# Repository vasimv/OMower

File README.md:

OMower project is open-source open-hardware wheeled robots platform with 32-bit ARM ATSAM3X8E
microcontroller, same as in Arduino Due. The project compiles under Arduino IDE (requires patching standard
ATSAM platform library files to support all GPIO lines of the MCU).

The project was inspired by ardumower project (https://github.com/Ardumower/ardumower) and uses few bits
of its code.

FEATURES

Control, measurements and navigation routines for wheeled robots (primarily lawn mowers but not limited to)
with wire perimeters, sonars and other sensors, GPS or RTK GPS (centimeters-level precision).

Support for 2 (with third support wheel) or 4 motors platforms. Brushed motors supported with Polulu Dual
MC33926 (onboard) or IHM12A1 controllers (external), brushless motors will require external ESCs (controlled
by PPM/servo output).

Includes PPM/servo output for the brushless mowing motor (or you may use onboard for brushed mowing motor)
and step-motor drivers for cutter's height adjusting.  

Supports many communication ports of ATSAM3X8E with onboard connectors to connect almost everything. 

It may operate with pure pfodApp (or Modbus) user interface but has limited support for Robot OS (ROS).

HARDWARE

The board is based on ATSAM3X8E-AU MCU in 144-pins LQFP case (for arduino IDE it looks like Arduino Due
without "programming" port).

Power subsystem includes step-down charging regulator (up to 4A charging current) and step-up for solar
battery, bi-stable relay for emergency shutdown. Has 3 switching regulators to provide 3.3V and 5V to
multiple internal and external devices, precise linear regulator for analog parts.

Supports battery voltages up to 28 volts, has onboard switching regulators for external charger and solar
panel.

Three ACS725-30 current hall sensors to measure consumption and charging currents up to 30A real-time.

Multiple connectors for everything mower or any other robot needed with 5V->3.3V logic conversion (6x HC-SR04
sonars, 5 odometers, 3 serial ports, 4 wire perimeter sensors, two bumper sensors, lawns and drops sensors,
two temperature NTC termistors connectors, two SPI ports, LEDs, button and more).

Has I2C buffers (both 3.3V and 5V versions) to connect multiple I2C devices, USB port (firmware upload),
external 12-channel ADC MAX11617 (connected to I2C).

Has port for Orange PI Zero (for RTK GPS and Wifi connectivity, firmware upload), can be replaced by any
Wifi/Bluetooth adapter connected to serial port of MCU.

Multiple PPM/servo outputs for external stuff with standard 3-pins connectors.

Note, board requires external components: external IMU GY-80 board or MPU-9250 board, external motors
controllers and steppig motor driver boards. External charger voltage must be 6 volts higher than
maximum battery voltage (i.e. for 14.6V LiFePo-battery it must provide 20..34V).

Latest version is 3, in v4 version the board will include FRAM chip to store settings/waypoints/etc (as
ATSAM3X8E's flash is getting erased when uploading new firmware) and onboard IMU MPU9250.

Schematics and KiCad development files for the 4-layers board is in hardware folder. Version 3 board
variant can be ordered from oshpark: https://oshpark.com/shared_projects/ILEdXK2T

SOFTWARE

The SDK's main goal is isolate hardware stuff from higher level software and easy development of wheeled
robot platforms. It configures timers, interrupts, ADCs and other stuff to provide API to develop software
without underlying hardware knowledge. It provides basic control and navigation stuff (like moving between
points with RTK GPS), external ports (like sonars or PPM/servo stuff), measurements for ADCs (internal and
onboard MAX11617), etc.

Look omower-*.h header files for API classes, check OMower_Simple firmware to see how to use them.

OMower SDK includes patches (see *.patch files) for standard ATSAM* libraries to support all GPIO's of
ATSAM3X8E (compatible GPIO mapping with Taijuino Due Pro). Without them you won't able to use all ports of
the OMower board!

Some of OMower stuff is not compatible with other arduino libraries, check restrictions.txt file.

Decawave DWM1000 radiotags navigation support is not tested yet, requires DWM1000 tags connected to MCU with
MyRangeTag software, see https://github.com/vasimv/MyRangeTag

USAGE

Place OMower folder into ~/Arduino/libraries, choose your board in omower-defs.h (currently supported boards
are OMower v3 and Arduino Due + IHM12A1 motor controller. Remember to patch ATSAM hardware library files to
use all GPIOs of ATSAM3X8E MCU.

Clone https://github.com/vasimv/OMower_Simple and  put its folder into ~/Arduino, compile and upload. Use
pfodApp to control the robot.

ROS support

At this moment, ROS support is limited and includes sending some of sensors data to ROS (with *MultiArray
messages but i planning to convert them to standartized message types), /cmd_vel support and routing debug and user
interface to ROS topics. See OMower_Simple firmware example on how to enable ROS in your firmware.

HOW IT WORKS

OMower software must define all needed objects, set pointers to other objects where it needed (like
gps object needs to set pointer to imu object), call all begin() functions of objects (hardware init, called
just once), then sets values for objects parameters and call init() functions (software init, can be
called many times to reset the object's hardware), define poll10/20/50 hooks functions to call objects
poll*() functions from there (see OMower_Simple.ino for example).

One of most important classes is motors object (see omower-motors.h), it controls motor drivers from its
poll10() function. User just calls functions roll/move (to simple turning or driving in a specific
direction) or rollCourse/MoveCourse to drive with navigation by something (compass, gps, etc). 

IMU stuff (compass, gyro, accelerometer) are read in imu object (omower-imu.h) by its poll50() function.
It does filtering/calculation and provide angle values for compass and pitch/yaw/roll in degrees
(see omower-imu.h). The imu object is daughter class of navThing class (see omower-root.h) that means
it has readCourseError() function, so it can be used for navigation by motors object. Currently it supports
navigation by compass angle.

GPS object is daughter class of navThing too, so it supports navigation. All coordinates are stored in
int32_t values (so, 18.3495,-68.5960 will be 183495000,-685960000 actually) to improve precision (otherwise
it would need large float class which does not exists in arduino framework). The user software must
interface with a GPS receiver and feed NMEA lines from it to gps::parseString() function or raw
coordinates to gps::settCoords() (see omower-gps.h). In precision mode (when centimeters-precise
coordinates are used) - the gps object calculates robot's true coordinates using offset of GPS's antenna
(distance from robot's center and angle).

Power object (omower-power.h) handles power stuff (battery, solar panel and charger regulators) and
provides human-readable values of voltages and currents.

Mow object (omower-mow.h) manages the mowing motor(s) and its actuator (if have) to adjust cutting height.
Note, currently it supports only PPM regulation on PWM-E output (brushless motors ESC connected to it), but
will support brushed motors too (in 2 wheel motors + mow motor configuration).

Perimeter object (omower-perimeter.h) supports up to 4 wire perimeter sensors (same as for ardumower, just
inductor+analog amplifier).

Serial object (omower-serial.h) handles communication with serial ports (as you can't use arduino's
objects for that because possible interrupts conflicts). It has also better printf() functions which
supports %f/%g for floats. UART (Serial.*) interface works with DMA (through built-in PDC) with huge
output buffer (2048 bytes, can be changed in omower-debug.h), so debug output function won't cause
slow-downs.

Sonars object (omower-sonars.h) handles HC-SR04 sonars (up to 6). It returns sonar's reported distance
(in centimeters) through its readSonar() function. Since motors routines do not check for any obstacles
during movement (except overcurrent on motors drivers), the user software must check sonars and bumpers
to avoid obstacles and move around them.

At start of initialization chassis object (omower-chassis.h) initializes interrupts. This is most important
task as almost all of OMower's stuff is done through interrupts hooks. It configures TIM7 to generate
interrupts 100 times per second.

At every TIM7 interrupt, it reads 12 channels of MAX11617 ADC to "uint16_t adc11617Arr[]"
(defined in max11617-adc-scan.h), this array is accessed from other OMower's objects (like power object, but
of course you can read its values directly).

Every second cycle of TIM7 interrupt it calls user's poll50() hook, at every fifth - poll20() hook, at
every tenth - poll10(). User's software must define these functions, set it through
chassis::setHooksPoll() function and call all other objects poll10/20/50 functions from there. By default,
to call hook functions it creates software interrupts for each kind of them (defined symbol
USE_SOFTWARE_INTERRUPTS in omower-defs-omowerv3.h), so they are running asynchronous. Without
USE_SOFTWARE_INTERRUPTS - poll50/20/10 hooks called after each other and you are limited to 20ms total time
for all of them (OMower SDK functions were optimized to comply with that time and software interrupts
can be turned off but if you place some other CPU hungry stuff in it - you will need software interrupts).

It was possible to create automatic binding for poll functions (so user wouldn't need to call all
objects poll*() functions from firmware code), but it was decided not to do so to simplify the SDK
internals.

All internal ADC channels of ATSAM3X8E are read by separate TIM5 interrupts 38461 times per second to the
"adcArr[]" array (see due-adc-scan.h for its structure). This array is accessed by other omower objects
from their poll10/20/50 functions, so no need to read it directly (but you still can do). Note, it is
possible to add circle buffer to every channel read, so you won't miss any of value (this method is used
in wire perimeter class for FFT filtering of the perimeter signal) through adcAddChannel()
function (due-adc-scan.h).

PWM and TCC (in PWM mode) outputs are configured through pwmServo object (omower-pwmservo.h), don't use
other methods to modify their output as it may conflict with OMower code. Since the code uses some
MCU's timers, you won't able to use these for other things (Timer0, Timer6, Timer8 in pwmServo, Timer5 in
due-adc-scan.cpp, Timer7 in chassis). Usually, nothing uses them but some of arduino libraries do (like
Servo library, which you wouldn't need as there is pwmServo object).

Debug function debug() is defined in omower-debug.h. By default, it sends its output to Serial device, has
ability to set priority for debug messages (so low-priority stuff won't be send at all).

There are some other objects which are easy to understand (omower-rtc.h for RTC clock, omower-current*.h for
current sensors, omower-odometry.h for odometry sensors), please, look their header files and OMower_Simple
firmware code if you want to know how they are used.

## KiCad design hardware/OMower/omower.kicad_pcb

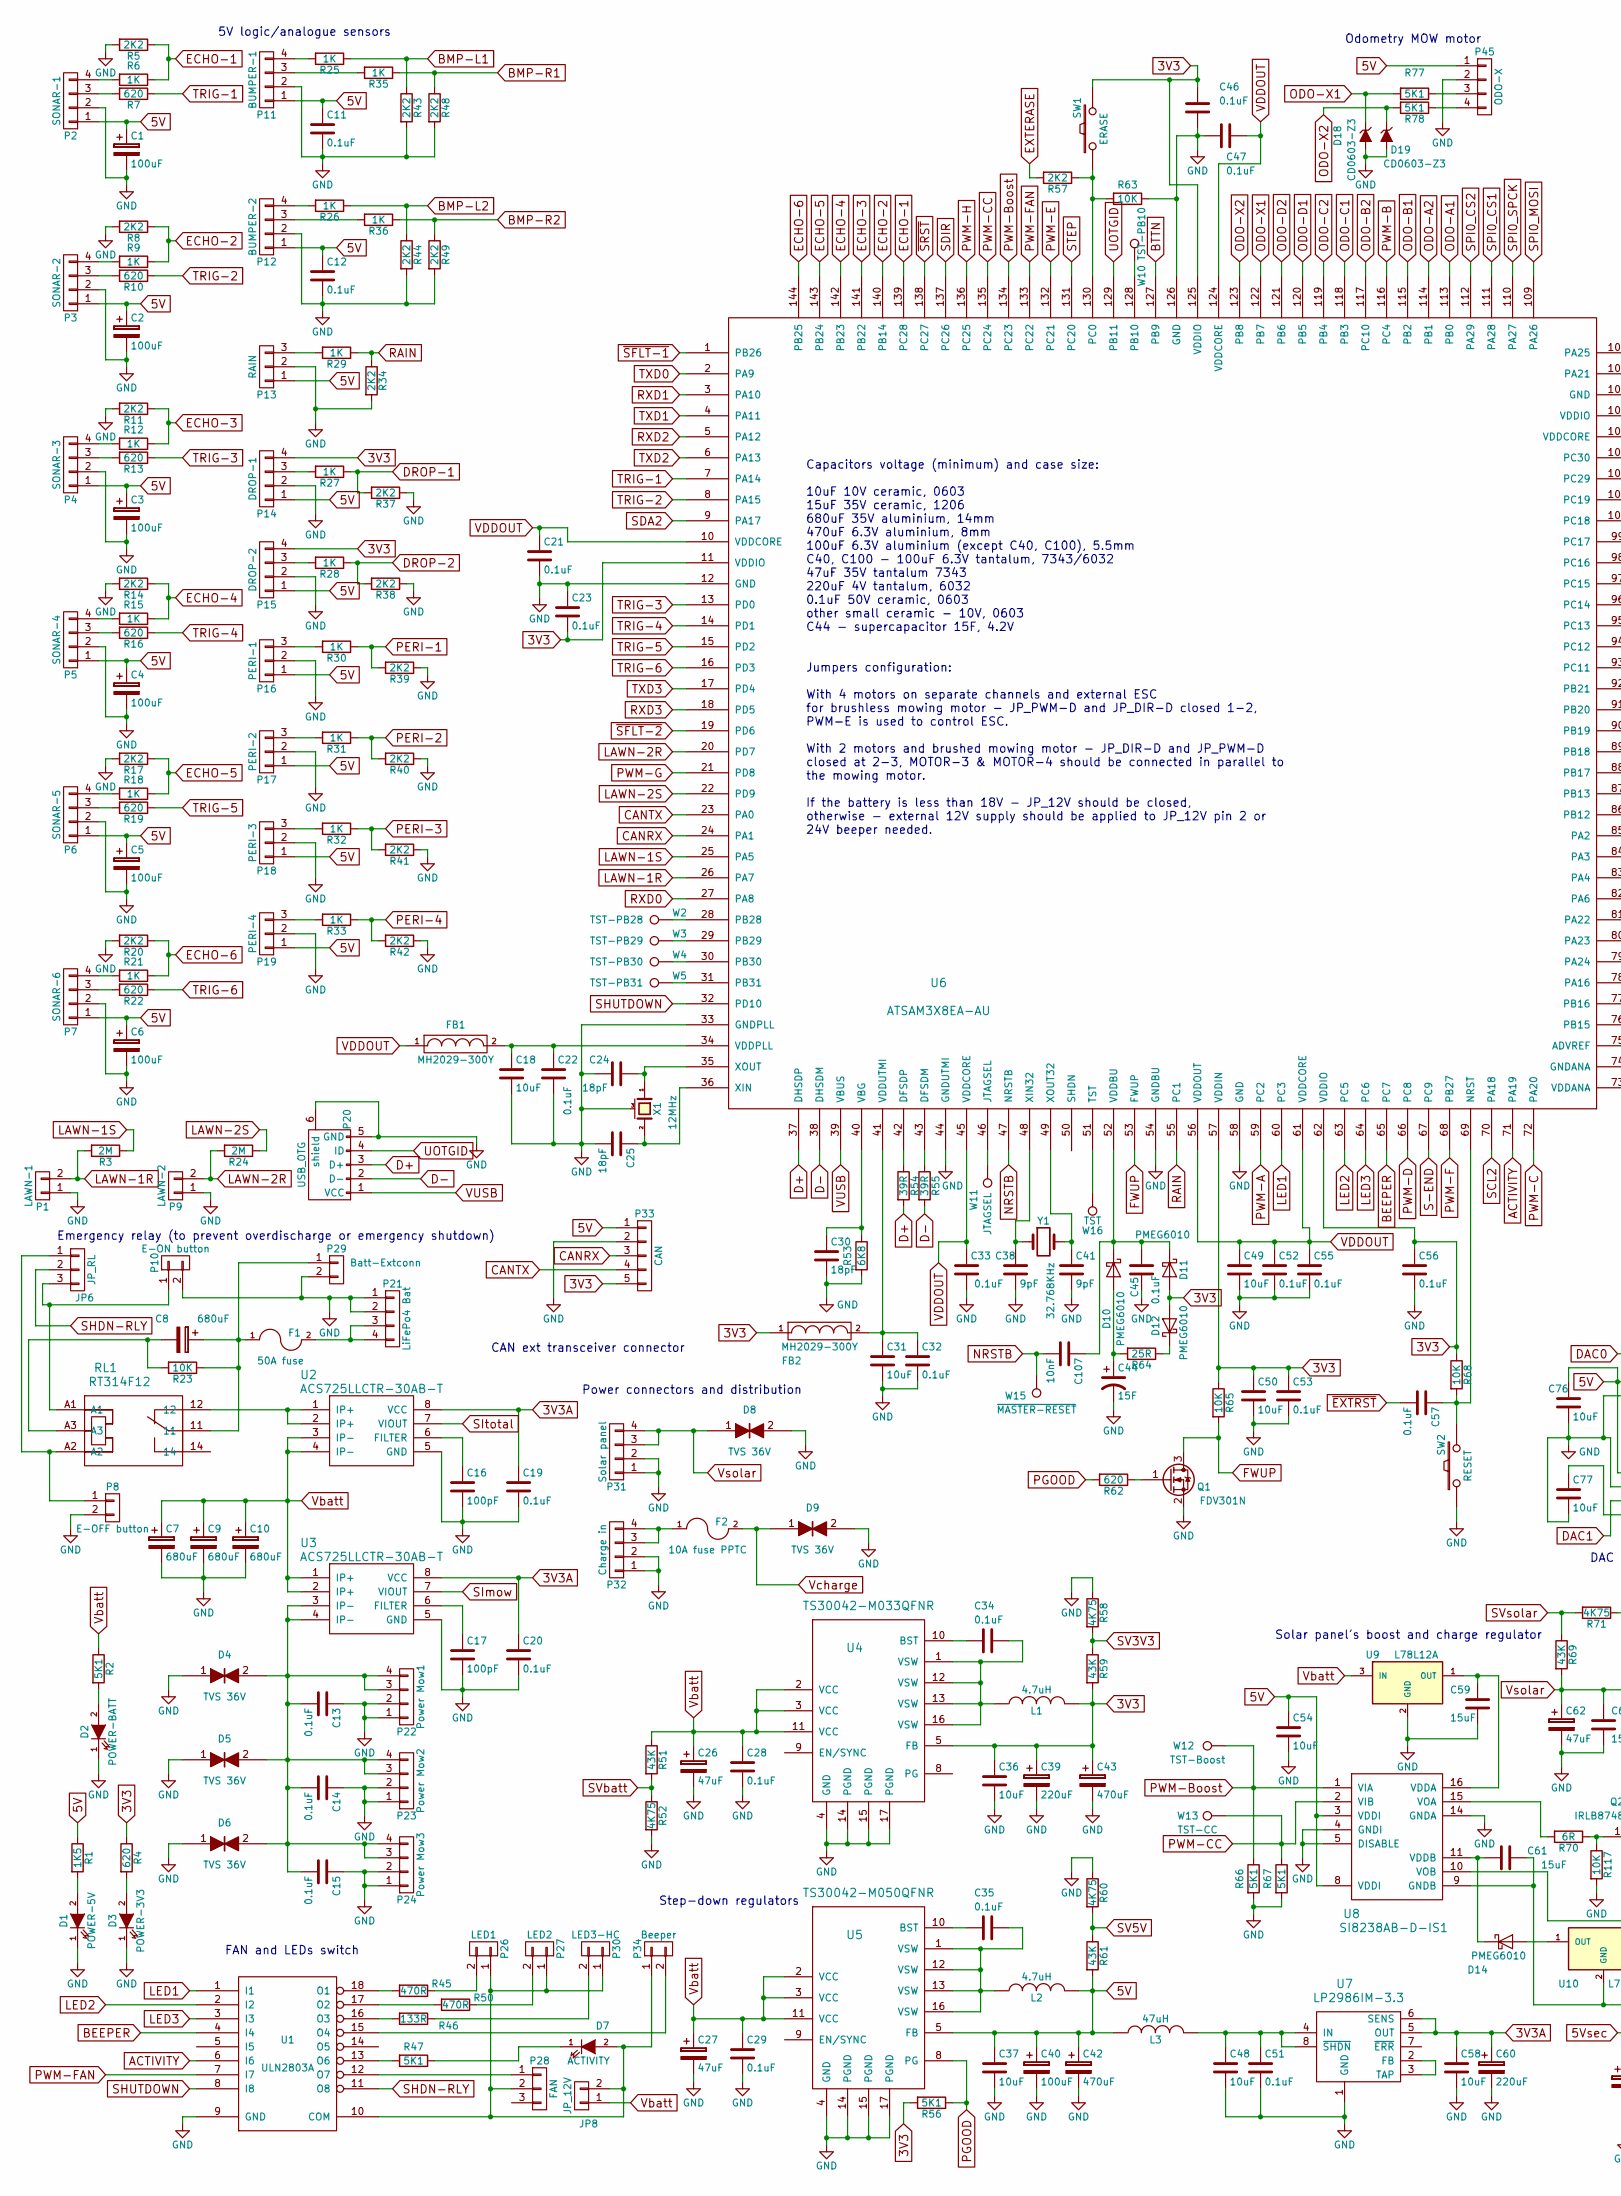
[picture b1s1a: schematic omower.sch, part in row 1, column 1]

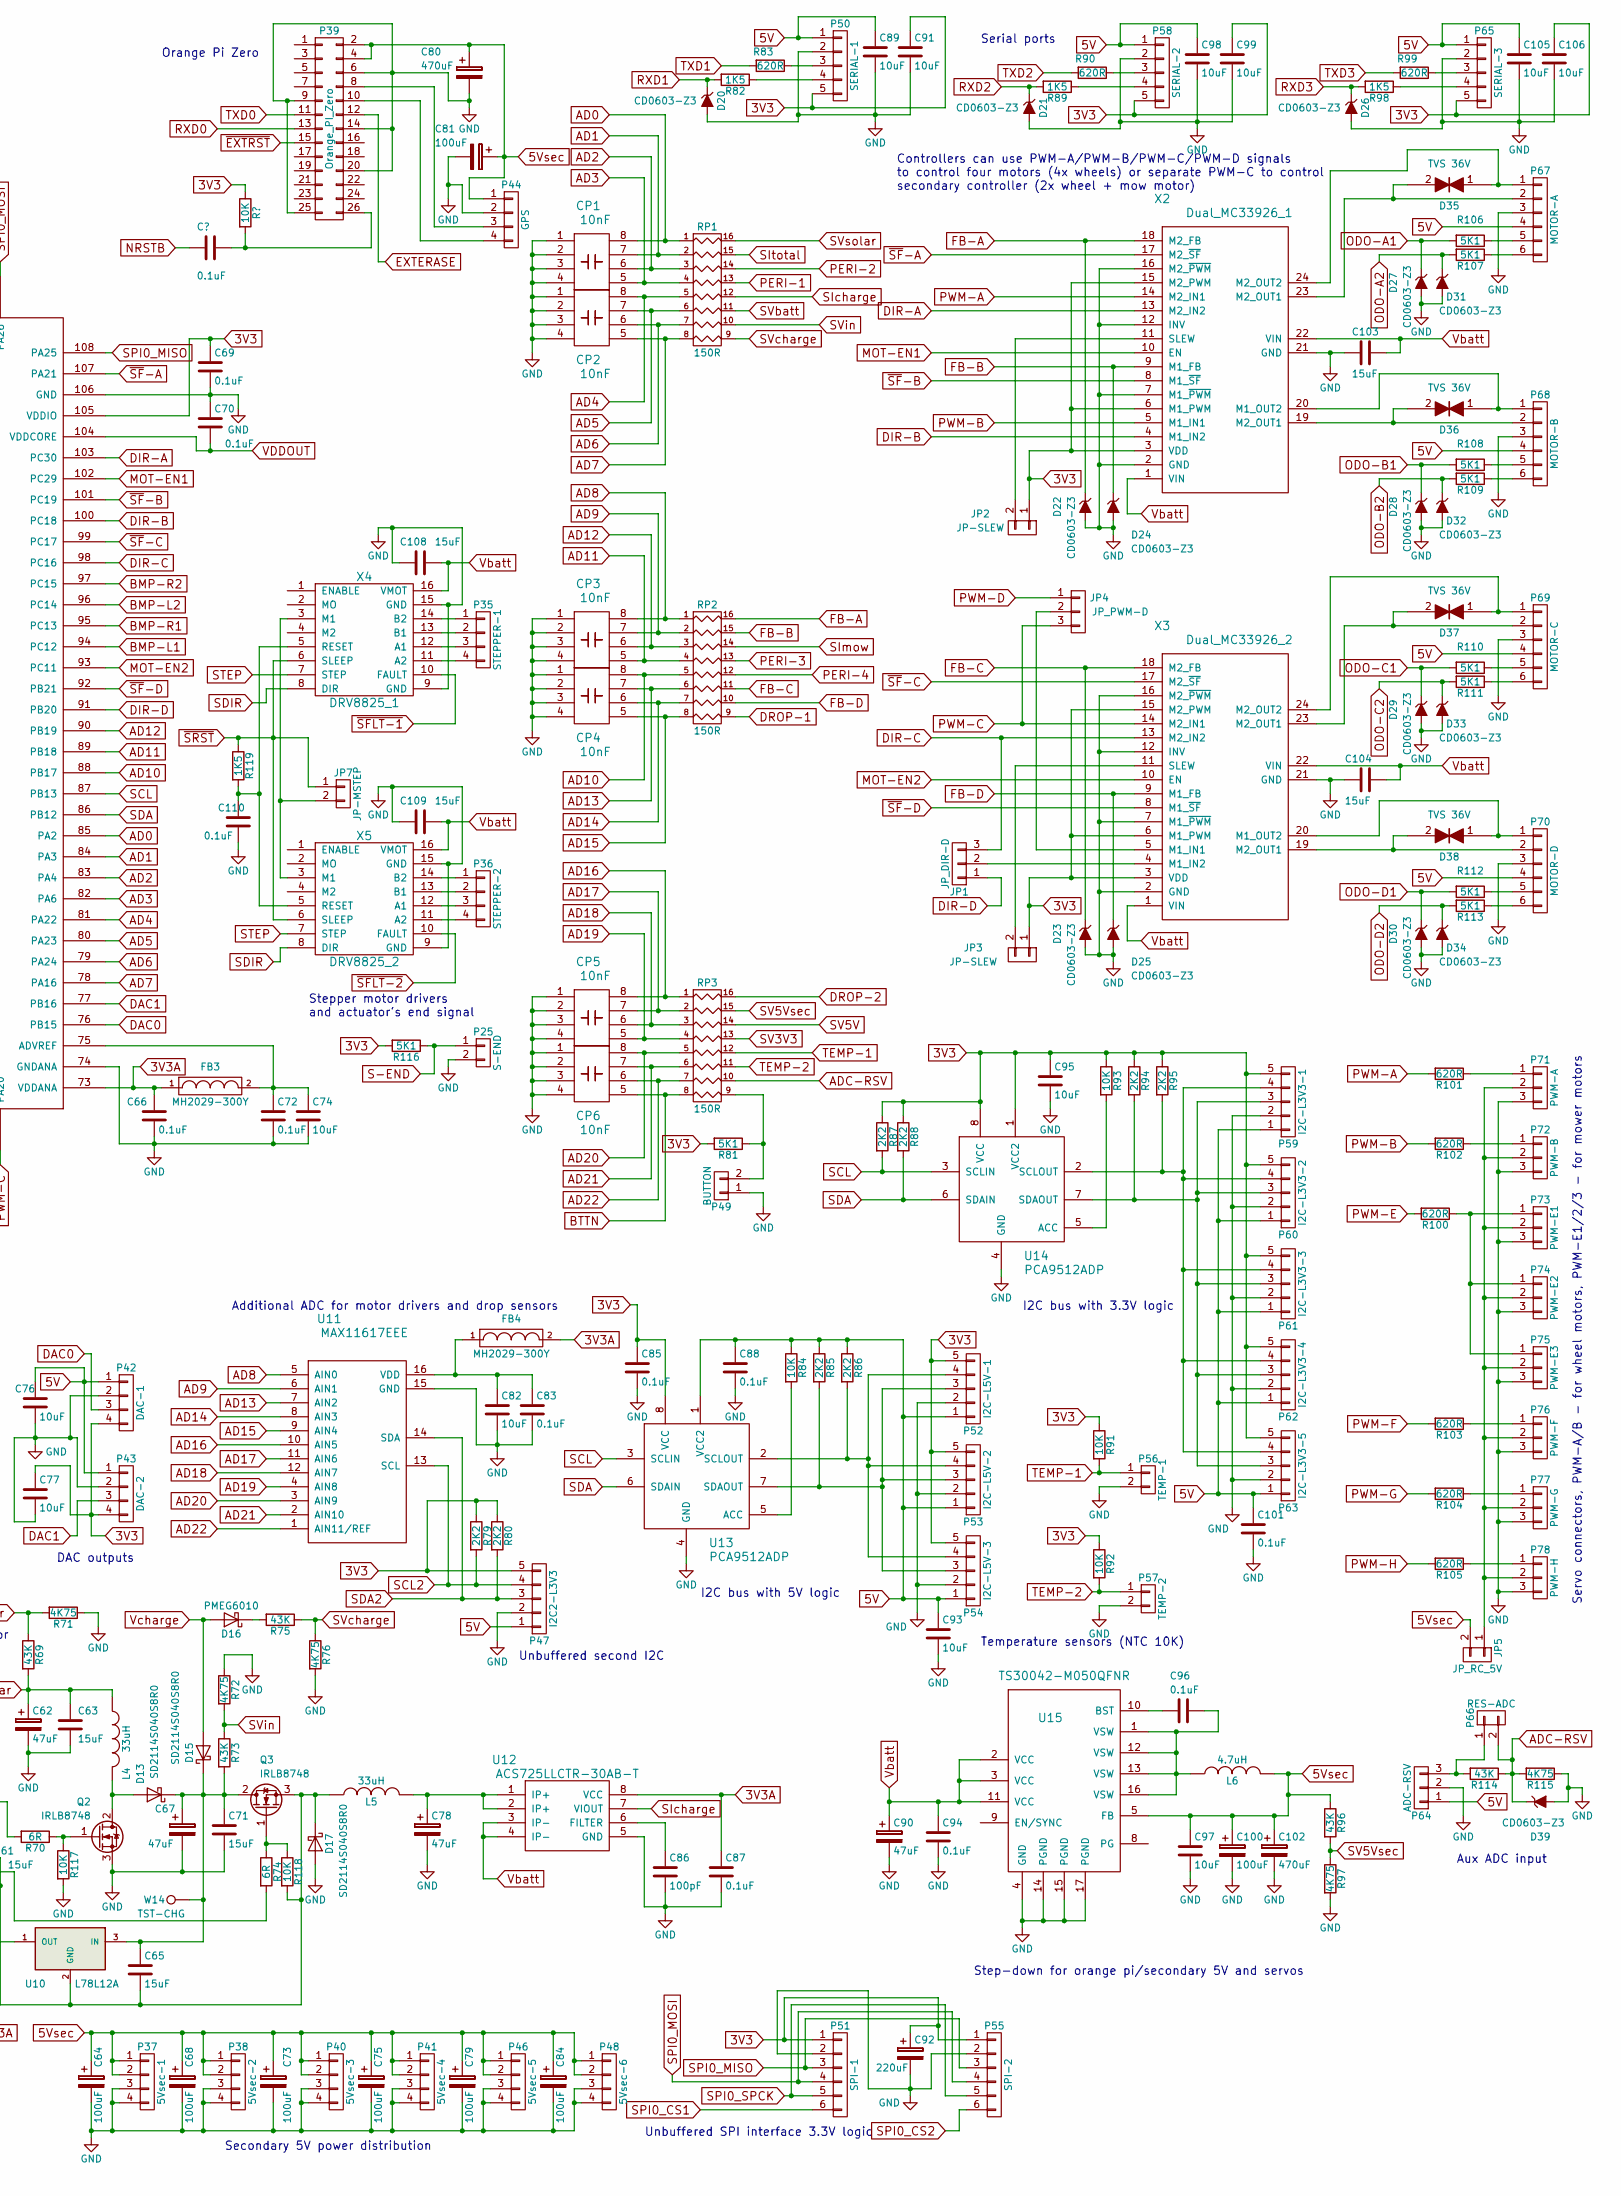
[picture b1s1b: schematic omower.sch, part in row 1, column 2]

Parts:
C1, C2, C3, C4, C5, C6, C64, C68, C73, C75, C79, C84: 100uF; c_elec_6.3x5.7; Voltage 6.3V
C7, C8, C9, C10: 680uF; CPCASE-12.5; Voltage 35V
C11, C12, C13, C14, C15, C19, C20, C28, C29, C51, C83, C87, C94, C101, C110: 0.1uF; C_0805
C16, C17, C86: 100pF; C_0805
C18, C31, C49, C50: 10uF; C_0603; Voltage 10V
C21, C22, C23, C32, C33, C34, C35, C45, C46, C47, C52, C53, C55, C56, C57, C66, C69, C70, C72, C85, C88, C96: 0.1uF; C_0603
C24, C25, C30: 18pF; C_0805
C26, C27, C62, C67, C78: 47uF; TantalC_SizeX_EIA-7343; Voltage 35V
C36, C37, C48, C54, C58, C82, C97: 10uF; C_1206
C38, C41: 9pF; C_0805
C39, C60, C92: 220uF; TantalC_SizeC_EIA-6032_Reflow; Voltage 4V
C40, C100: 100uF; TantalC_SizeD_EIA-7343_Reflow; Voltage 6.3V
C42, C80, C102: 470uF; c_elec_8x10.5; Voltage 6.3V
C43: 470uF; c_elec_8x10.5; Voltage 4V
C44: 15F; Supercap-Vishay_E3_22_24; Voltage 4.2V
C59, C61, C63, C65, C71: 15uF; C_1206; Voltage 35V
C74, C89, C91, C98, C99, C105, C106: 10uF; C_1206; Voltage 10V
C76, C77, C95: 10uF; C_0603
C81: 100uF; TantalC_SizeD_EIA-7343_Reflow
C90: 47uF; TantalC_SizeX_EIA-7343; Voltage 10V
C93: 10uF; C_0805
C103, C104: 15uF; C_0805
C107: 10nF; C_0805
C108, C109: 15uF; C_1206
CP1, CP2, CP3, CP4, CP5, CP6: 10nF; R_Array_Concave_4x0402
D1: POWER-5V; LED-3MM
D2: POWER-BATT; LED-3MM
D3: POWER-3V3; LED-3MM
D4, D5, D6, D8, D9, D35, D36, D37, D38: TVS 36V; R_0402
D7: ACTIVITY; LED-3MM
D10, D11, D12, D14, D16: PMEG6010; SOD-123
D13, D15, D17: SD2114S040S8R0; SMB_Standard
D18, D19, D20, D21, D22, D23, D24, D25, D26, D27, D28, D29, D30, D31, D32, D33, D34, D39: CD0603-Z3; SOD-523
F1: 50A fuse; MAXI-Fuse-Clip-29.21
F2: 10A fuse PPTC; RV_Disc_D21.5_W5.3_P10
FB1, FB2, FB3, FB4: MH2029-300Y; R_0805
JP1: JP_DIR-D; Pin_Header_Straight_1x03
JP2, JP3: JP-SLEW; Pin_Header_Straight_1x02
JP4: JP_PWM-D; Pin_Header_Straight_1x03
JP5: JP_RC_5V; Pin_Header_Straight_1x02
JP6: JP_RL; Pin_Header_Straight_1x03
JP7: JP-MSTEP; Pin_Header_Straight_1x02
JP8: JP_12V; Pin_Header_Straight_1x02
L1, L2, L6: 4.7uH; Choke_SMD_Wuerth-WE-PD2-Typ-MS
L3: 47uH; Choke_SMD_7.3x7.3_H3.5
L4, L5: 33uH; Choke-PG1096
P1: LAWN-1; Pin_Header_Straight_1x02
P2: SONAR-1; Pin_Header_Straight_1x04
P3: SONAR-2; Pin_Header_Straight_1x04
P4: SONAR-3; Pin_Header_Straight_1x04
P5: SONAR-4; Pin_Header_Straight_1x04
P6: SONAR-5; Pin_Header_Straight_1x04
P7: SONAR-6; Pin_Header_Straight_1x04
P8: E-OFF button; Pin_Header_Straight_1x02
P9: LAWN-2; Pin_Header_Straight_1x02
P10: E-ON button; Pin_Header_Straight_1x02
P11: BUMPER-1; Pin_Header_Straight_1x04
P12: BUMPER-2; Pin_Header_Straight_1x04
P13: RAIN; Pin_Header_Straight_1x03
P14: DROP-1; Pin_Header_Straight_1x04
P15: DROP-2; Pin_Header_Straight_1x04
P16: PERI-1; Pin_Header_Straight_1x03
P17: PERI-2; Pin_Header_Straight_1x03
P18: PERI-3; Pin_Header_Straight_1x03
P19: PERI-4; Pin_Header_Straight_1x03
P20: USB_OTG; USB_Micro-B_10103594-0001LF
P21: LiFePo4 Bat; Molex_MiniFit-JR-5569-04A2_2x02x4.20mm_Angled
P22: Power Mow1; Molex_MiniFit-JR-5569-04A2_2x02x4.20mm_Angled
P23: Power Mow2; Molex_MiniFit-JR-5569-04A2_2x02x4.20mm_Angled
P24: Power Mow3; Molex_MiniFit-JR-5569-04A2_2x02x4.20mm_Angled
P25: S-END; Pin_Header_Straight_1x02
P26: LED1; Pin_Header_Straight_1x02
P27: LED2; Pin_Header_Straight_1x02
P28: FAN; Pin_Header_Straight_1x03
P29: Batt-Extconn; Pin_Header_Straight_1x02
P30: LED3-HC; Pin_Header_Straight_1x02
P31: Solar panel; Molex_MiniFit-JR-5569-04A2_2x02x4.20mm_Angled
P32: Charge in; Molex_MiniFit-JR-5569-04A2_2x02x4.20mm_Angled
P33: CAN; Pin_Header_Straight_1x05
P34: Beeper; Pin_Header_Straight_1x02
P35: STEPPER-1; Pin_Header_Straight_1x04
P36: STEPPER-2; Pin_Header_Straight_1x04
P37: 5Vsec-1; Pin_Header_Straight_1x04
P38: 5Vsec-2; Pin_Header_Straight_1x04
P39: Orange_PI_Zero; Pin_Header_Straight_2x13
P40: 5Vsec-3; Pin_Header_Straight_1x04
P41: 5Vsec-4; Pin_Header_Straight_1x04
P42: DAC-1; Pin_Header_Straight_1x04
P43: DAC-2; Pin_Header_Straight_1x04
P44: GPS; Pin_Header_Straight_1x04
P45: ODO-X; Pin_Header_Straight_1x04
P46: 5Vsec-5; Pin_Header_Straight_1x04
P47: I2C2-L3V3; Pin_Header_Straight_1x05
P48: 5Vsec-6; Pin_Header_Straight_1x04
P49: BUTTON; Pin_Header_Straight_1x02
P50: SERIAL-1; Pin_Header_Straight_1x05
P51: SPI-1; Pin_Header_Straight_1x06
P52: I2C-L5V-1; Pin_Header_Straight_1x05
P53: I2C-L5V-2; Pin_Header_Straight_1x05
P54: I2C-L5V-3; Pin_Header_Straight_1x05
P55: SPI-2; Pin_Header_Straight_1x06
P56: TEMP-1; Pin_Header_Straight_1x02
P57: TEMP-2; Pin_Header_Straight_1x02
P58: SERIAL-2; Pin_Header_Straight_1x05
P59: I2C-L3V3-1; Pin_Header_Straight_1x05
P60: I2C-L3V3-2; Pin_Header_Straight_1x05
P61: I2C-L3V3-3; Pin_Header_Straight_1x05
P62: I2C-L3V3-4; Pin_Header_Straight_1x05
P63: I2C-L3V3-5; Pin_Header_Straight_1x05
P64: ADC-RSV; Pin_Header_Straight_1x03
P65: SERIAL-3; Pin_Header_Straight_1x05
P66: RES-ADC; Pin_Header_Straight_1x02
P67: MOTOR-A; Pin_Header_Straight_1x06
P68: MOTOR-B; Pin_Header_Straight_1x06
P69: MOTOR-C; Pin_Header_Straight_1x06
P70: MOTOR-D; Pin_Header_Straight_1x06
P71: PWM-A; Pin_Header_Straight_1x03
P72: PWM-B; Pin_Header_Straight_1x03
P73: PWM-E1; Pin_Header_Straight_1x03
P74: PWM-E2; Pin_Header_Straight_1x03
P75: PWM-E3; Pin_Header_Straight_1x03
P76: PWM-F; Pin_Header_Straight_1x03
P77: PWM-G; Pin_Header_Straight_1x03
P78: PWM-H; Pin_Header_Straight_1x03
Q1: FDV301N; SOT-23
Q2, Q3: IRLB8748; TO-220_Neutral123_Horizontal_LargePads
R1, R82, R89, R98, R119: 1K5; R_0603
R2, R47, R56, R66, R67, R77, R78, R81, R106, R107, R108, R109, R110, R111, R112, R113, R116: 5K1; R_0603
R3, R24: 2M; R_0603
R4, R7, R10, R13, R16, R19, R22, R62: 620; R_0603
R5, R8, R11, R14, R17, R20, R34, R37, R38, R39, R40, R41, R42, R43, R44, R48, R49, R57, R79, R80, R85, R86, R87, R88, R94, R95: 2K2; R_0603
R6, R9, R12, R15, R18, R21, R25, R26, R27, R28, R29, R30, R31, R32, R33, R35, R36: 1K; R_0603
R23, R63, R65, R68, R84, R91, R92, R93, R117, R118: 10K; R_0603
R45, R50: 470R; R_0805
R46: 133R; R_0805
R51, R59, R61, R69, R73, R75, R96, R114: 43K; R_0603
R52, R58, R60, R71, R72, R76, R97, R115: 4K75; R_0603
R53: 6K8; R_0603
R54, R55: 39R; R_0603
R64: 25R; R_0603
R70, R74: 6R; R_0805
R83, R90, R99, R100, R101, R102, R103, R104, R105: 620R; R_0603
RL1: RT314F12; Relay_RT314F12
RP1, RP2, RP3: 150R; R_Array_Convex_8x0602
SW1: ERASE; SW_SPST_EVQPE1
SW2: RESET; SW_SPST_EVQPE1
U1: ULN2803A; SOIC-18_7.5x11.6mm_Pitch1.27mm
U2, U3, U12: ACS725LLCTR-30AB-T; SOIC-8-N
U4: TS30042-M033QFNR; QFN-16-1EP_3x3mm_Pitch0.5mm
U5, U15: TS30042-M050QFNR; QFN-16-1EP_3x3mm_Pitch0.5mm
U6: ATSAM3X8EA-AU; LQFP-144_20x20mm_Pitch0.5mm
U7: LP2986IM-3.3; SOIC-8-N
U8: SI8238AB-D-IS1; SOIC-16_3.9x9.9mm_Pitch1.27mm
U9, U10: L78L12A; SOT89-3_Housing
U11: MAX11617EEE; QSOP-16_3.9x4.9mm_Pitch0.635mm
U13, U14: PCA9512ADP; MSOP-8_3x3mm_Pitch0.65mm
W2: TST-PB28; Wirepad_SMD_2x2mm
W3: TST-PB29; Wirepad_SMD_2x2mm
W4: TST-PB30; Wirepad_SMD_2x2mm
W5: TST-PB31; Wirepad_SMD_2x2mm
W10: TST-PB10; Wirepad_SMD_2x2mm
W11: JTAGSEL; Wirepad_SMD_2x2mm
W12: TST-Boost; Pin_Header_Straight_1x01
W13: TST-CC; Pin_Header_Straight_1x01
W14: TST-CHG; Pin_Header_Straight_1x01
W15: ~MASTER-RESET; Pin_Header_Straight_1x01
W16: TST; Wirepad_SMD_2x2mm
X1: 12MHz; crystal_FA238-TSX3225
X2: Dual_MC33926_1; POLULU-DUAL_MC33926
X3: Dual_MC33926_2; POLULU-DUAL_MC33926
X4: DRV8825_1; POLOLU-DRV8825
X5: DRV8825_2; POLOLU-DRV8825
Y1: 32.768KHz; R_1206

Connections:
3V3: C23.2, C36.1, C39.1, C43.1, C46.1, C50.1, C53.1, C56.1, C69.1, C77.1, C85.1, C91.1, C92.1, C95.1, C99.1, C106.1, D11.2 (A), D12.2 (A), FB2.1, JP2.1, JP3.1, L1.2, P14.4, P15.4, P33.5, P42.4, P43.4, P47.5, P50.5, P51.1, P52.5, P53.5, P54.5, P55.1, P58.5, P59.5, P60.5, P61.5, P62.5, P63.5, P65.5, R4.1, R56.2, R59.2, R65.1, R68.1, R79.1, R80.1, R81.2, R87.1, R88.1, R91.1, R92.1, R93.1, R94.1, R95.1, R116.2, SW1.2, U4.5 (FB), U6.11 (VDDIO), U6.57 (VDDIN), U6.62 (VDDIO), U6.105 (VDDIO), U6.125 (VDDIO), U13.8 (VCC), U14.1 (VCC2), U14.8 (VCC), X2.3 (VDD), X2.6 (M1_PWM), X2.15 (M2_PWM), X3.3 (VDD), X3.6 (M1_PWM), X3.15 (M2_PWM)
3V3A: C19.1, C20.1, C58.1, C60.1, C66.1, C87.1, FB3.1, FB4.2, U2.8 (VCC), U3.8 (VCC), U6.73 (VDDANA), U7.5 (OUT), U7.6 (SENS), U12.8 (VCC)
5V: C1.1, C2.1, C3.1, C4.1, C5.1, C6.1, C11.1, C12.1, C37.1, C40.1, C42.1, C54.1, C76.1, C88.1, C89.1, C93.1, C98.1, C101.1, C105.1, L2.2, L3.1, P2.1, P3.1, P4.1, P5.1, P6.1, P7.1, P11.1, P12.1, P13.1, P14.1, P15.1, P16.1, P17.1, P18.1, P19.1, P33.1, P42.1, P43.1, P45.1, P47.1, P50.1, P52.1, P53.1, P54.1, P58.1, P59.1, P60.1, P61.1, P62.1, P63.1, P64.1, P65.1, P67.4, P68.4, P69.4, P70.4, R1.1, R61.2, R84.1, R85.1, R86.1, U5.5 (FB), U8.3 (VDDI), U8.8 (VDDI), U13.1 (VCC2)
5Vsec: C64.1, C68.1, C73.1, C75.1, C79.1, C80.1, C81.1, C84.1, C97.1, C100.1, C102.1, JP5.2, L6.2, P37.1, P37.2, P38.1, P38.2, P39.2, P39.4, P40.1, P40.2, P41.1, P41.2, P44.1, P46.1, P46.2, P48.1, P48.2, R96.1, U15.5 (FB)
ACTIVITY: U1.6 (I6), U6.71 (PA19)
AD0: CP1.8, RP1.1, U6.85 (PA2)
AD1: CP1.7, RP1.2, U6.84 (PA3)
AD2: CP1.6, RP1.3, U6.83 (PA4)
AD3: CP1.5, RP1.4, U6.82 (PA6)
AD4: CP2.8, RP1.5, U6.81 (PA22)
AD5: CP2.7, RP1.6, U6.80 (PA23)
AD6: CP2.6, RP1.7, U6.79 (PA24)
AD7: CP2.5, RP1.8, U6.78 (PA16)
AD8: CP3.8, RP2.1, U11.5 (AIN0)
AD9: CP3.7, RP2.2, U11.6 (AIN1)
AD10: CP4.8, RP2.5, U6.88 (PB17)
AD11: CP3.5, RP2.4, U6.89 (PB18)
AD12: CP3.6, RP2.3, U6.90 (PB19)
AD13: CP4.7, RP2.6, U11.7 (AIN2)
AD14: CP4.6, RP2.7, U11.8 (AIN3)
AD15: CP4.5, RP2.8, U11.9 (AIN4)
AD16: CP5.8, RP3.1, U11.10 (AIN5)
AD17: CP5.7, RP3.2, U11.11 (AIN6)
AD18: CP5.6, RP3.3, U11.12 (AIN7)
AD19: CP5.5, RP3.4, U11.4 (AIN8)
AD20: CP6.8, RP3.5, U11.3 (AIN9)
AD21: CP6.7, RP3.6, U11.2 (AIN10)
AD22: CP6.6, RP3.7, U11.1 (AIN11/REF)
ADC-RSV: D39.1 (K), P66.2, R114.1, R115.2, RP3.10 (R7)
BEEPER: U1.4 (I4), U6.65 (PC7)
BMP-L1: R25.1, R43.1, U6.94 (PC12)
BMP-L2: R26.1, R44.1, U6.96 (PC14)
BMP-R1: R35.1, R48.1, U6.95 (PC13)
BMP-R2: R36.1, R49.1, U6.97 (PC15)
BTTN: CP6.5, RP3.8, U6.127 (PB9)
CANRX: P33.3, U6.24 (PA1)
CANTX: P33.4, U6.23 (PA0)
D+: P20.3 (D+), R54.2, U6.37 (DHSDP)
D-: P20.2 (D-), R55.2, U6.38 (DHSDM)
DAC0: P42.3, U6.76 (PB15)
DAC1: P43.3, U6.77 (PB16)
DIR-A: U6.103 (PC30), X2.13 (M2_IN2)
DIR-B: U6.100 (PC18), X2.4 (M1_IN2)
DIR-C: JP1.3, U6.98 (PC16), X3.13 (M2_IN2)
DIR-D: JP1.1, U6.91 (PB20)
DROP-1: R27.1, R37.2, RP2.9 (R8)
DROP-2: R28.1, R38.2, RP3.16 (R1)
ECHO-1: R5.1, R6.1, U6.139 (PC28)
ECHO-2: R8.1, R9.1, U6.140 (PB14)
ECHO-3: R11.1, R12.1, U6.141 (PB22)
ECHO-4: R14.1, R15.1, U6.142 (PB23)
ECHO-5: R17.1, R18.1, U6.143 (PB24)
ECHO-6: R20.1, R21.1, U6.144 (PB25)
EXTERASE: P39.12, R57.2
FB-A: D22.1 (K), RP2.16 (R1), X2.18 (M2_FB)
FB-B: D24.1 (K), RP2.15 (R2), X2.9 (M1_FB)
FB-C: D23.1 (K), RP2.11 (R6), X3.18 (M2_FB)
FB-D: D25.1 (K), RP2.10 (R7), X3.9 (M1_FB)
FWUP: Q1.3 (D), R65.2, U6.53 (FWUP)
GND: C1.2, C2.2, C3.2, C4.2, C5.2, C6.2, C7.2, C9.2, C10.2, C11.2, C12.2, C13.1, C14.1, C15.1, C16.2, C17.2, C18.2, C19.2, C20.2, C21.2, C22.2, C23.1, C24.2, C25.2, C26.2, C27.2, C28.2, C29.2, C30.2, C31.2, C32.2, C33.2, C36.2, C37.2, C38.2, C39.2, C40.2, C41.2, C42.2, C43.2, C44.2, C45.2, C46.2, C47.2, C48.2, C49.2, C50.2, C51.2, C52.2, C53.2, C54.2, C55.2, C56.2, C58.2, C59.2, C60.2, C62.2, C63.2, C64.2, C66.2, C67.2, C68.2, C69.2, C70.1, C71.2, C72.2, C73.2, C74.2, C75.2, C76.2, C77.2, C78.2, C79.2, C80.2, C81.2, C82.2, C83.2, C84.2, C85.2, C86.2, C87.2, C88.2, C89.2, C90.2, C91.2, C92.2, C93.2, C94.2, C95.2, C97.2, C98.2, C99.2, C100.2, C101.2, C102.2, C103.2, C104.2, C105.2, C106.2, C108.2, C109.2, C110.2, CP1.1, CP1.2, CP1.3, CP1.4, CP2.1, CP2.2, CP2.3, CP2.4, CP3.1, CP3.2, CP3.3, CP3.4, CP4.1, CP4.2, CP4.3, CP4.4, CP5.1, CP5.2, CP5.3, CP5.4, CP6.1, CP6.2, CP6.3, CP6.4, D1.1 (K), D2.1 (K), D3.1 (K), D4.1, D5.1, D6.1, D8.2, D9.2, D17.2 (A), D18.2 (A), D19.2 (A), D20.2 (A), D21.2 (A), D22.2 (A), D23.2 (A), D24.2 (A), D25.2 (A), D26.2 (A), D27.2 (A), D28.2 (A)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
LAWN-1R: P1.2, R3.2, U6.26 (PA7)
LAWN-1S: R3.1, U6.25 (PA5)
LAWN-2R: P9.2, R24.2, U6.20 (PD7)
LAWN-2S: R24.1, U6.22 (PD9)
LED1: U1.1 (I1), U6.60 (PC3)
LED2: U1.2 (I2), U6.63 (PC5)
LED3: U1.3 (I3), U6.64 (PC6)
MOT-EN1: U6.102 (PC29), X2.10 (EN)
MOT-EN2: U6.93 (PC11), X3.10 (EN)
NRSTB: C107.2, U6.47 (NRSTB), W15.1
unnamed: C8.1, F1.1, P29.1, R23.1, RL1.11
unnamed: C13.2, C14.2, C15.2, D4.2, D5.2, D6.2, P22.3, P22.4, P23.3, P23.4, P24.3, P24.4, U3.3 (IP-), U3.4 (IP-)
unnamed: C16.1, U2.6 (FILTER)
unnamed: C17.1, U3.6 (FILTER)
unnamed: C18.1, C22.1, FB1.2, U6.34 (VDDPLL)
unnamed: C24.1, U6.35 (XOUT), X1.1
unnamed: C25.1, U6.36 (XIN), X1.2
unnamed: C30.1, R53.1, U6.40 (VBG)
unnamed: C31.1, C32.1, FB2.2, U6.41 (VDDUTMI)
unnamed: C34.1, L1.1, U4.1 (VSW), U4.12 (VSW), U4.13 (VSW), U4.16 (VSW)
unnamed: C34.2, U4.10 (BST)
unnamed: C35.1, L2.1, U5.1 (VSW), U5.12 (VSW), U5.13 (VSW), U5.16 (VSW)
unnamed: C35.2, U5.10 (BST)
unnamed: C38.1, U6.48 (XIN32), Y1.1
unnamed: C41.1, U6.49 (XOUT32), Y1.2
unnamed: C44.1, D10.2 (A), R64.2
unnamed: C48.1, C51.1, L3.2, U7.4 (IN), U7.8 (~SHDN)
unnamed: C57.1, R68.2, SW2.2, U6.69 (NRST)
unnamed: C59.1, U8.16 (VDDA), U9.1 (OUT)
unnamed: C61.1, C65.2, D17.1 (K), L5.1, Q3.3 (S), R118.2, U8.9 (GNDB), U10.2 (GND)
unnamed: C72.1, C74.1, FB3.2, U6.75 (ADVREF)
unnamed: C78.1, L5.2, U12.1 (IP+), U12.2 (IP+)
unnamed: C82.1, C83.1, FB4.1, U11.16 (VDD)
unnamed: C86.1, U12.6 (FILTER)
unnamed: C96.1, L6.1, U15.1 (VSW), U15.12 (VSW), U15.13 (VSW), U15.16 (VSW)
unnamed: C96.2, U15.10 (BST)
unnamed: C45.1, C107.1, D10.1 (K), D11.1 (K), U6.52 (VDDBU)
unnamed: C110.1, R119.2, X4.5 (RESET), X5.5 (RESET)
unnamed: D1.2 (A), R1.2
unnamed: D2.2 (A), R2.2
unnamed: D3.2 (A), R4.2
unnamed: D7.1 (K), R47.1
unnamed: D7.2 (A), JP8.2, P26.1, P27.1, P28.2, P30.1, P34.1, U1.10 (COM)
unnamed: D12.1 (K), R64.1
unnamed: D13.2 (A), L4.2, Q2.2 (D)
unnamed: D16.1 (K), R75.2
unnamed: D35.1, P67.1, X2.24 (M2_OUT2)
unnamed: D35.2, P67.2, X2.23 (M2_OUT1)
unnamed: D36.1, P68.1, X2.20 (M1_OUT2)
unnamed: D36.2, P68.2, X2.19 (M2_OUT1)
unnamed: D37.1, P69.1, X3.24 (M2_OUT2)
unnamed: D37.2, P69.2, X3.23 (M2_OUT1)
unnamed: D38.1, P70.1, X3.20 (M1_OUT2)
unnamed: D38.2, P70.2, X3.19 (M2_OUT1)
unnamed: F1.2, P21.3, P21.4
unnamed: F2.1, P32.3, P32.4
unnamed: JP1.2, X3.4 (M1_IN2)
unnamed: JP2.2, X2.11 (SLEW)
unnamed: JP3.2, X3.11 (SLEW)
unnamed: JP4.2, X3.5 (M1_IN1)
unnamed: JP5.1, P71.2, P72.2, P73.2, P74.2, P75.2, P76.2, P77.2, P78.2
unnamed: JP6.3, P10.1, RL1.A1
unnamed: JP7.2, X4.3 (M1), X5.3 (M1)
unnamed: P2.3, R7.2
unnamed: P2.4, R6.2
unnamed: P3.3, R10.2
unnamed: P3.4, R9.2
unnamed: P4.3, R13.2
unnamed: P4.4, R12.2
unnamed: P5.3, R16.2
unnamed: P5.4, R15.2
unnamed: P6.3, R19.2
unnamed: P6.4, R18.2
unnamed: P7.3, R22.2
unnamed: P7.4, R21.2
unnamed: P11.3, R35.2
unnamed: P11.4, R25.2
unnamed: P12.3, R36.2
unnamed: P12.4, R26.2
unnamed: P13.3, R29.2
unnamed: P14.3, R27.2
unnamed: P15.3, R28.2
unnamed: P16.3, R30.2
unnamed: P17.3, R31.2
unnamed: P18.3, R32.2
unnamed: P19.3, R33.2
unnamed: P26.2, R45.1
unnamed: P27.2, R50.1
unnamed: P28.1, U1.12 (O7)
unnamed: P30.2, R46.1
unnamed: P34.2, U1.15 (O4)
unnamed: P35.1, X4.14 (B2)
unnamed: P35.2, X4.13 (B1)
unnamed: P35.3, X4.12 (A1)
unnamed: P35.4, X4.11 (A2)
unnamed: P36.1, X5.14 (B2)
unnamed: P36.2, X5.13 (B1)
unnamed: P36.3, X5.12 (A1)
unnamed: P36.4, X5.11 (A2)
unnamed: P39.8, P44.3
unnamed: P39.10, P44.4
unnamed: P45.3, R77.1
unnamed: P45.4, R78.1
unnamed: P49.2, R81.1, RP3.9 (R8)
unnamed: P50.3, R83.1
unnamed: P50.4, R82.1
unnamed: P52.3, P53.3, P54.3, R85.2, U13.7 (SDAOUT)
unnamed: P52.4, P53.4, P54.4, R86.2, U13.2 (SCLOUT)
unnamed: P58.3, R90.1
unnamed: P58.4, R89.1
unnamed: P59.3, P60.3, P61.3, P62.3, P63.3, R94.2, U14.7 (SDAOUT)
unnamed: P59.4, P60.4, P61.4, P62.4, P63.4, R95.2, U14.2 (SCLOUT)
unnamed: P64.3, P66.1, R114.2
unnamed: P65.3, R99.1
unnamed: P65.4, R98.1
unnamed: P67.5, R106.1
unnamed: P67.6, R107.1
unnamed: P68.5, R108.1
unnamed: P68.6, R109.1
unnamed: P69.5, R110.1
unnamed: P69.6, R111.1
unnamed: P70.5, R112.1
unnamed: P70.6, R113.1
unnamed: P71.1, R101.1
unnamed: P72.1, R102.1
unnamed: P73.1, P74.1, P75.1, R100.1
unnamed: P76.1, R103.1
unnamed: P77.1, R104.1
unnamed: P78.1, R105.1
unnamed: Q1.1 (G), R62.1
unnamed: Q2.1 (G), R70.1, R117.1
unnamed: Q3.1 (G), R74.1, R118.1
unnamed: R45.2, U1.18 (O1)
unnamed: R46.2, U1.16 (O3)
unnamed: R47.2, U1.13 (O6)
unnamed: R50.2, U1.17 (O2)
unnamed: R54.1, U6.42 (DFSDP)
unnamed: R55.1, U6.43 (DFSDM)
unnamed: R57.1, R63.2, SW1.1, U6.130 (PC0)
unnamed: R70.2, U8.15 (VOA)
unnamed: R74.2, U8.10 (VOB)
unnamed: R84.2, U13.5 (ACC)
unnamed: R93.2, U14.5 (ACC)
unnamed: RL1.12, U2.1 (IP+), U2.2 (IP+)
unnamed: U6.28 (PB28), W2.1
unnamed: U6.29 (PB29), W3.1
unnamed: U6.30 (PB30), W4.1
unnamed: U6.31 (PB31), W5.1
unnamed: U6.46 (JTAGSEL), W11.1
unnamed: U6.51 (TST), W16.1
unnamed: U6.128 (PB10), W10.1
unnamed: U7.2 (FB), U7.3 (TAP)
ODO-A1: D27.1 (K), R106.2, U6.113 (PB0)
ODO-A2: D31.1 (K), R107.2, U6.114 (PB1)
ODO-B1: D28.1 (K), R108.2, U6.115 (PB2)
ODO-B2: D32.1 (K), R109.2, U6.117 (PC10)
ODO-C1: D29.1 (K), R110.2, U6.118 (PB3)
ODO-C2: D33.1 (K), R111.2, U6.119 (PB4)
ODO-D1: D30.1 (K), R112.2, U6.120 (PB5)
ODO-D2: D34.1 (K), R113.2, U6.121 (PB6)
ODO-X1: D18.1 (K), R77.2, U6.122 (PB7)
ODO-X2: D19.1 (K), R78.2, U6.123 (PB8)
PERI-1: R30.1, R39.2, RP1.13 (R4)
PERI-2: R31.1, R40.2, RP1.14 (R3)
PERI-3: R32.1, R41.2, RP2.13 (R4)
PERI-4: R33.1, R42.2, RP2.12 (R5)
PGOOD: R56.1, R62.2, U5.8 (PG)
PWM-A: R101.2, U6.59 (PC2), X2.14 (M2_IN1)
PWM-B: R102.2, U6.116 (PC4), X2.5 (M1_IN1)
PWM-Boost: R66.1, U6.134 (PC23), U8.1 (VIA), W12.1
PWM-C: JP4.3, U6.72 (PA20), X3.14 (M2_IN1)
PWM-CC: R67.1, U6.135 (PC24), U8.2 (VIB), W13.1
PWM-D: JP4.1, U6.66 (PC8)
PWM-E: R100.2, U6.132 (PC21)
PWM-F: R103.2, U6.68 (PB27)
PWM-FAN: U1.7 (I7), U6.133 (PC22)
PWM-G: R104.2, U6.21 (PD8)
PWM-H: R105.2, U6.136 (PC25)
RAIN: R29.1, R34.1, U6.55 (PC1)
RXD0: P39.13, U6.27 (PA8)
RXD1: D20.1 (K), R82.2, U6.3 (PA10)
RXD2: D21.1 (K), R89.2, U6.5 (PA12)
RXD3: D26.1 (K), R98.2, U6.18 (PD5)
S-END: P25.1, R116.1, U6.67 (PC9)
SCL: R87.2, U6.87 (PB13), U13.3 (SCLIN), U14.3 (SCLIN)
SCL2: P47.4, R79.2, U6.70 (PA18), U11.13 (SCL)
SDA: R88.2, U6.86 (PB12), U13.6 (SDAIN), U14.6 (SDAIN)
SDA2: P47.3, R80.2, U6.9 (PA17), U11.14 (SDA)
SDIR: U6.137 (PC26), X4.8 (DIR), X5.8 (DIR)
SHDN-RLY: JP6.2, U1.11 (O8)
SHUTDOWN: U1.8 (I8), U6.32 (PD10)
SIcharge: RP1.12 (R5), U12.7 (VIOUT)
SImow: RP2.14 (R3), U3.7 (VIOUT)
SItotal: RP1.15 (R2), U2.7 (VIOUT)
SPI0_CS1: P51.6, U6.111 (PA28)
SPI0_CS2: P55.6, U6.112 (PA29)
SPI0_MISO: P51.3, P55.3, U6.108 (PA25)
SPI0_MOSI: P51.4, P55.4, U6.109 (PA26)
SPI0_SPCK: P51.5, P55.5, U6.110 (PA27)
STEP: U6.131 (PC20), X4.7 (STEP), X5.7 (STEP)
SV3V3: R58.2, R59.1, RP3.13 (R4)
SV5V: R60.2, R61.1, RP3.14 (R3)
SV5Vsec: R96.2, R97.1, RP3.15 (R2)
SVbatt: R51.2, R52.1, RP1.11 (R6)
SVcharge: R75.1, R76.1, RP1.9 (R8)
SVin: R72.2, R73.1, RP1.10 (R7)
SVsolar: R69.1, R71.2, RP1.16 (R1)
TEMP-1: P56.1, R91.2, RP3.12 (R5)
TEMP-2: P57.1, R92.2, RP3.11 (R6)
TRIG-1: R7.1, U6.7 (PA14)
TRIG-2: R10.1, U6.8 (PA15)
TRIG-3: R13.1, U6.13 (PD0)
TRIG-4: R16.1, U6.14 (PD1)
TRIG-5: R19.1, U6.15 (PD2)
TRIG-6: R22.1, U6.16 (PD3)
TXD0: P39.11, U6.2 (PA9)
TXD1: R83.2, U6.4 (PA11)
TXD2: R90.2, U6.6 (PA13)
TXD3: R99.2, U6.17 (PD4)
UOTGID: P20.4 (ID), U6.129 (PB11)
VDDOUT: C21.1, C33.1, C47.1, C49.1, C52.1, C55.1, C70.2, FB1.1, U6.10 (VDDCORE), U6.45 (VDDCORE), U6.56 (VDDOUT), U6.61 (VDDCORE), U6.104 (VDDCORE), U6.124 (VDDCORE)
VUSB: P20.1 (VCC), U6.39 (VBUS)
Vbatt: C7.1, C9.1, C10.1, C26.1, C27.1, C28.1, C29.1, C90.1, C94.1, C103.1, C104.1, C108.1, C109.1, JP8.1, R2.1, R51.1, U2.3 (IP-), U2.4 (IP-), U3.1 (IP+), U3.2 (IP+), U4.2 (VCC), U4.3 (VCC), U4.11 (VCC), U5.2 (VCC), U5.3 (VCC), U5.11 (VCC), U9.3 (IN), U12.3 (IP-), U12.4 (IP-), U15.2 (VCC), U15.3 (VCC), U15.11 (VCC), X2.1 (VIN), X2.22 (VIN), X3.1 (VIN), X3.22 (VIN), X4.16 (VMOT), X5.16 (VMOT)
Vcharge: D9.1, D15.2 (A), D16.2 (A), F2.2
Vsolar: C62.1, C63.1, D8.1, L4.1, P31.3, P31.4, R69.2
~EXTRST: C57.2, P39.15
~SFLT-1: U6.1 (PB26), X4.10 (FAULT)
~SFLT-2: U6.19 (PD6), X5.10 (FAULT)
~SF~-A: U6.107 (PA21), X2.17 (M2_~SF)
~SF~-B: U6.101 (PC19), X2.8 (M1_~SF)
~SF~-C: U6.99 (PC17), X3.17 (M2_~SF)
~SF~-D: U6.92 (PB21), X3.8 (M1_~SF)
~SRST: JP7.1, R119.1, U6.138 (PC27), X4.6 (SLEEP), X5.6 (SLEEP)

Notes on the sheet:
Power connectors and distribution
Step-down regulators
Solar panel's boost and charge regulator
Step-down for orange pi/secondary 5V and servos
Controllers can use PWM-A/PWM-B/PWM-C/PWM-D signals to control four motors (4x wheels) or separate PWM-C to control secondary controller (2x wheel + mow motor)
Servo connectors, PWM-A/B - for wheel motors, PWM-E1/2/3 - for mower motors
I2C bus with 5V logic
I2C bus with 3.3V logic
Emergency relay (to prevent overdischarge or emergency shutdown)
Unbuffered second I2C
Additional ADC for motor drivers and drop sensors
5V logic/analogue sensors
Aux ADC input
Temperature sensors (NTC 10K)
Secondary 5V power distribution
FAN and LEDs switch
Serial ports
Orange Pi Zero
Unbuffered SPI interface 3.3V logic
DAC outputs
CAN ext transceiver connector
Odometry MOW motor
Stepper motor drivers and actuator's end signal
Capacitors voltage (minimum) and case size: 10uF 10V ceramic, 0603 15uF 35V ceramic, 1206 680uF 35V aluminium, 14mm 470uF 6.3V aluminium, 8mm 100uF 6.3V aluminium (except C40, C100), 5.5mm C40, C100 - 100uF 6.3V tantalum, 7343/6032 47uF 35V tantalum 7343 220uF 4V tantalum, 6032 0.1uF 50V ceramic, 0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

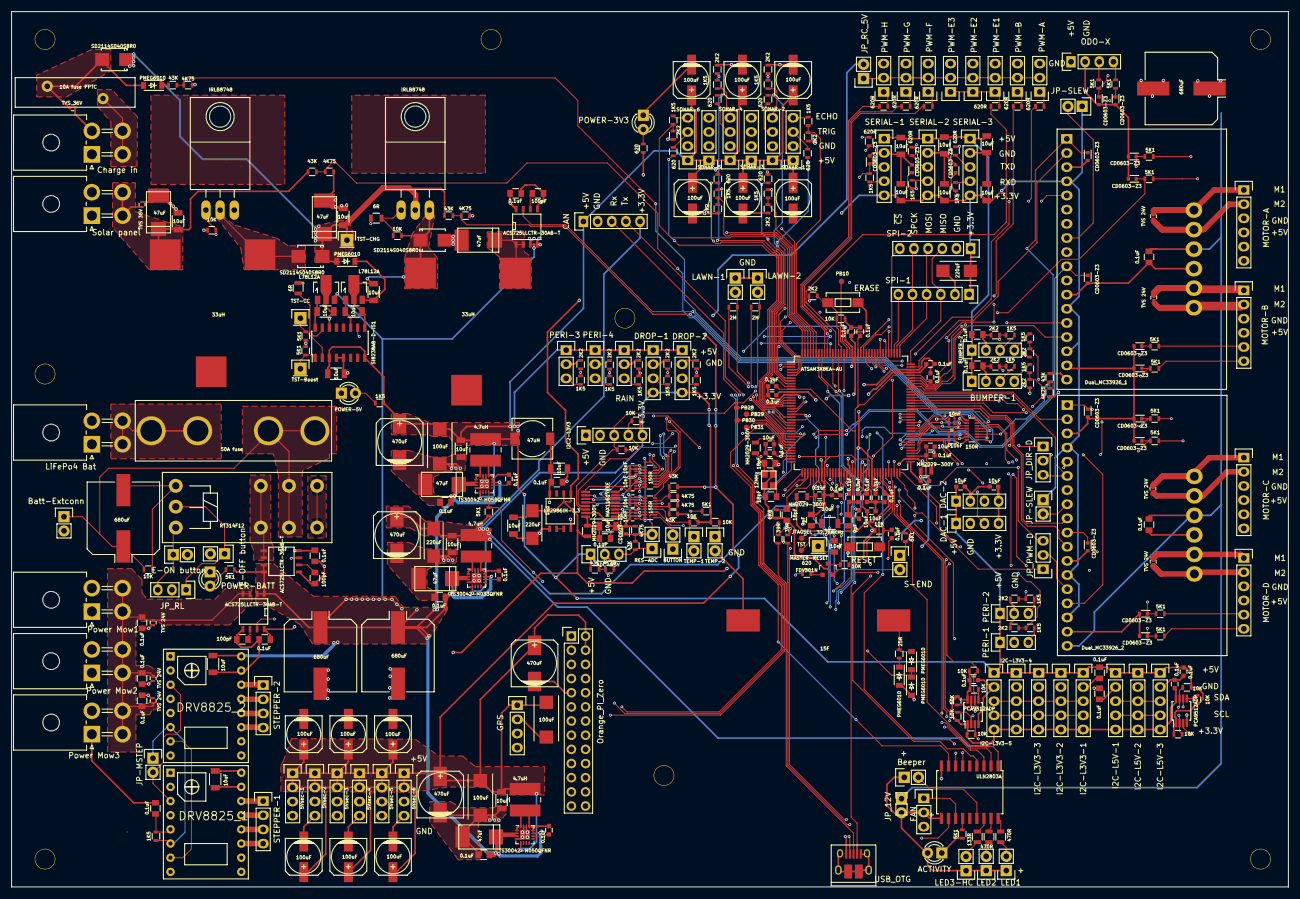
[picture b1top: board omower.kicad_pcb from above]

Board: 4 copper layers, 229.0 x 157.0 mm, 413 parts (0 on the bottom side), 298 nets.
